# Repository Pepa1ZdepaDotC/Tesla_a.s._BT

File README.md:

# Tesla 1128A repair and BT upgrade
 **Goals:**
 - Repair radio into its original state.
 - Add a MCU capable of BT
 - Enhance the entire radio with, for example LCD, modern AMP IC

[Schematic](https://github.com/Pepa1ZdepaDotC/Tesla_BT/blob/main/Tesla_rev_2/Tesla_sextant_BT.pdf)

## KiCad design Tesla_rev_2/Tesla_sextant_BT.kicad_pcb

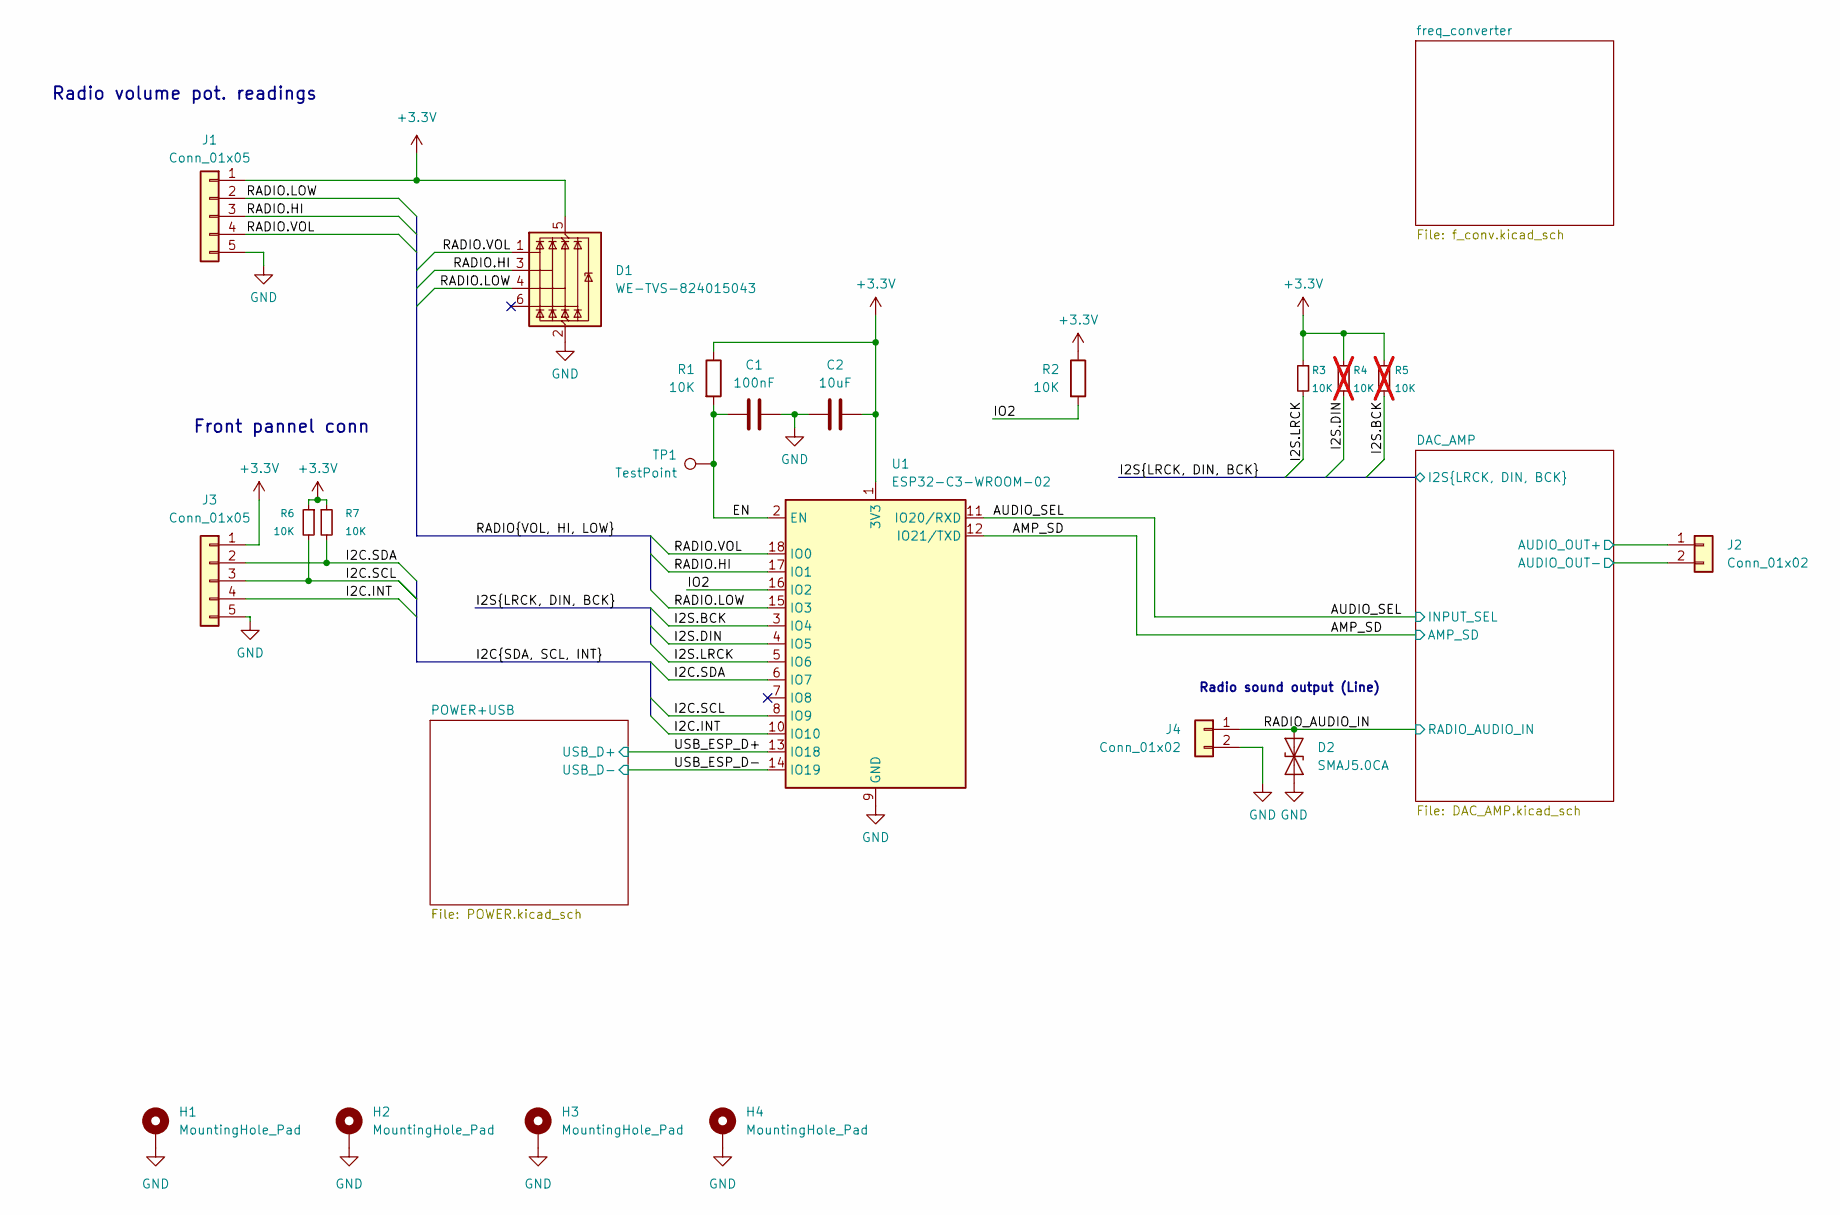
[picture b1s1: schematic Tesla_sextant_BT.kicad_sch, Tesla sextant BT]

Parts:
C1: 100nF; C_0805_2012Metric
C2: 10uF; C_0805_2012Metric
D1: WE-TVS-824015043; SOT-23-6
D2: SMAJ5.0CA; D_SMA
H1, H2, H3, H4: MountingHole_Pad; MountingHole_4.3mm_M4_DIN965_Pad_TopBottom
J1, J3: Conn_01x05; PinSocket_1x05_P2.00mm_Vertical
J2, J4: Conn_01x02; Conn_Solder_1x02_SMD
R1, R2, R3, R6, R7: 10K; C_0805_2012Metric
R4, R5: 10K; C_0805_2012Metric; not fitted
TP1: TestPoint; TestPoint_Pad_D2.5mm
U1: ESP32-C3-WROOM-02

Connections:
+3.3V: C2.1, D1.5 (VBUS), J1.1, J3.1, R1.1, R2.1, R3.1, R4.1, R5.1, R6.1, R7.1, U1.1 (3V3); also elsewhere on the board
/AMP_SD: U1.12 (IO21/TXD); also elsewhere on the board
/AUDIO_SEL: U1.11 (IO20/RXD); also elsewhere on the board
/DAC_AMP/AUDIO_OUT+: J2.1; also elsewhere on the board
/DAC_AMP/AUDIO_OUT-: J2.2; also elsewhere on the board
/EN: C1.2, R1.2, TP1.1, U1.2 (EN)
/I2C.INT: J3.4, U1.10 (IO10)
/I2C.SCL: J3.3, R6.2, U1.8 (IO9)
/I2C.SDA: J3.2, R7.2, U1.6 (IO7)
/I2S.BCK: R5.2, U1.3 (IO4); also elsewhere on the board
/I2S.DIN: R4.2, U1.4 (IO5); also elsewhere on the board
/I2S.LRCK: R3.2, U1.5 (IO6); also elsewhere on the board
/IO2: R2.2, U1.16 (IO2)
/RADIO.HI: D1.3 (I/O2), J1.3, U1.17 (IO1)
/RADIO.LOW: D1.4 (I/O3), J1.2, U1.15 (IO3)
/RADIO.VOL: D1.1 (I/O1), J1.4, U1.18 (IO0)
/RADIO_AUDIO_IN: D2.1 (A1), J4.1; also elsewhere on the board
/USB_ESP_D+: U1.13 (IO18); also elsewhere on the board
/USB_ESP_D-: U1.14 (IO19); also elsewhere on the board
GND: C1.1, C2.2, D1.2 (GND), D2.2 (A2), H1.1, H2.1, H3.1, H4.1, J1.5, J3.5, J4.2, U1.9 (GND), U1.19 (GND); also elsewhere on the board

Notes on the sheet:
Radio volume pot. readings
Radio sound output (Line)
Front pannel conn

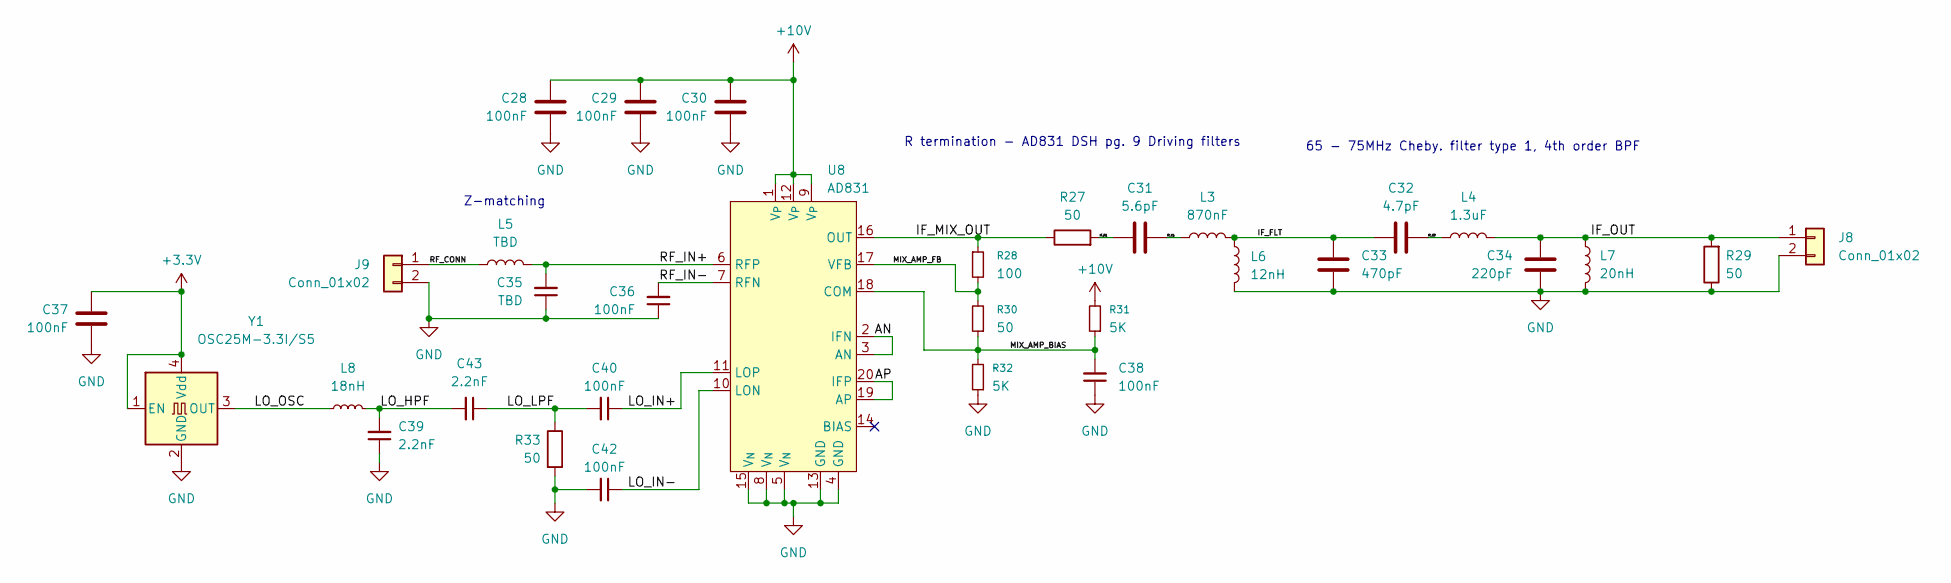
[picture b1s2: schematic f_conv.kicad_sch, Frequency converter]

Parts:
C28, C29, C30, C36, C37, C38: 100nF; C_0805_2012Metric
C31: 5.6pF; C_0603_1608Metric
C32: 4.7pF; C_0603_1608Metric
C33: 470pF; C_0603_1608Metric
C34: 220pF; C_0603_1608Metric
C35: TBD; C_0805_2012Metric
C39, C43: 2.2nF; C_0603_1608Metric
C40, C42: 100nF; C_0603_1608Metric
J8, J9: Conn_01x02; Conn_Solder_1x02_SMD
L3: 870nF; L_0805_2012Metric; Part_num DL0805-0.082
L4: 1.3uF; L_0805_2012Metric; Part_num DL0805-1.2
L5: TBD; L_0603_1608Metric
L6: 12nH; L_0603_1608Metric; Part_num LQG18HN12NJ00D
L7: 20nH; L_0603_1608Metric
L8: 18nH; L_0603_1608Metric
R27, R29, R30, R33: 50; C_0805_2012Metric
R28: 100; C_0805_2012Metric
R31, R32: 5K; C_0805_2012Metric
U8: AD831; PLCC-20
Y1: OSC25M-3.3I/S5; Oscillator_SMD_Fordahl_DFAS15-4Pin_5.0x3.2mm_HandSoldering

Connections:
+3.3V: C37.2, Y1.1 (EN), Y1.4 (Vdd); also elsewhere on the board
+10V: C28.2, C29.2, C30.2, R31.2, U8.1 (V_{P}), U8.9 (V_{P}), U8.12 (V_{P}); also elsewhere on the board
/freq_converter/AN: U8.2 (IFN), U8.3 (AN)
/freq_converter/AP: U8.19 (AP), U8.20 (IFP)
/freq_converter/IF_C1: C31.2, L3.2
/freq_converter/IF_C3: C32.1, L4.2
/freq_converter/IF_FLT: C32.2, C33.2, L3.1, L6.2
/freq_converter/IF_MIX_OUT: R27.1, R28.1, U8.16 (OUT)
/freq_converter/IF_OUT: C34.2, J8.1, L4.1, L7.1, R29.2
/freq_converter/IF_R1: C31.1, R27.2
/freq_converter/LO_HPF: C39.2, C43.2, L8.2
/freq_converter/LO_IN+: C40.1, U8.11 (LOP)
/freq_converter/LO_IN-: C42.1, U8.10 (LON)
/freq_converter/LO_LPF: C40.2, C43.1, R33.1
/freq_converter/LO_OSC: L8.1, Y1.3 (OUT)
/freq_converter/MIX_AMP_BIAS: C38.2, R30.1, R31.1, R32.2, U8.18 (COM)
/freq_converter/MIX_AMP_FB: R28.2, R30.2, U8.17 (VFB)
/freq_converter/RF_CONN: J9.1, L5.2
/freq_converter/RF_IN+: C35.2, L5.1, U8.6 (RFP)
/freq_converter/RF_IN-: C36.2, U8.7 (RFN)
GND: C28.1, C29.1, C30.1, C33.1, C34.1, C35.1, C36.1, C37.1, C38.1, C39.1, C42.2, J8.2, J9.2, L6.1, L7.2, R29.1, R32.1, R33.2, U8.4 (GND), U8.5 (V_{N}), U8.8 (V_{N}), U8.13 (GND), U8.15 (V_{N}), Y1.2 (GND); also elsewhere on the board

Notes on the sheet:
R termination - AD831 DSH pg. 9 Driving filters
65 - 75MHz Cheby. filter type 1, 4th order BPF
Z-matching

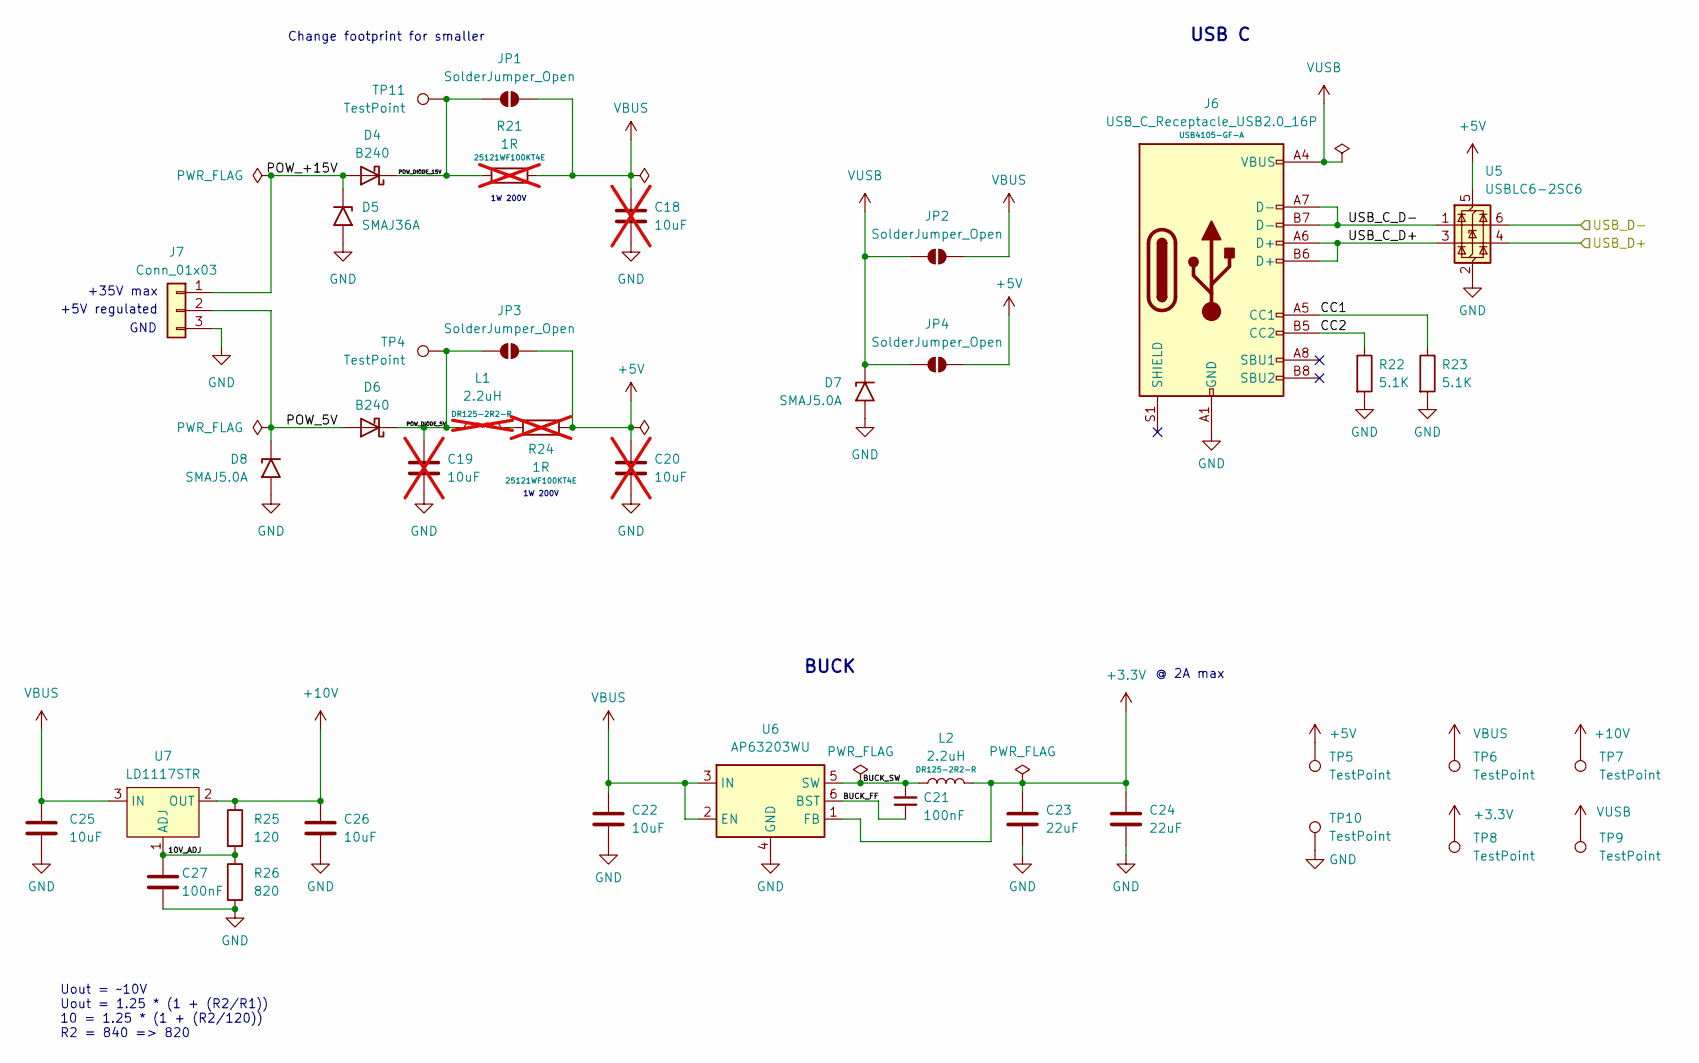
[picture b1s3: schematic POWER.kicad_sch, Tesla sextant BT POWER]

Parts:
C18, C19, C20: 10uF; C_0805_2012Metric; not fitted
C21, C27: 100nF; C_0805_2012Metric
C22, C25, C26: 10uF; C_0805_2012Metric
C23, C24: 22uF; C_0805_2012Metric
D4, D6: B240; D_SMB
D5: SMAJ36A; D_SMA
D7, D8: SMAJ5.0A; D_SMA
J6: USB_C_Receptacle_USB2.0_16P; USB_C_Receptacle_GCT_USB4105-xx-A_16P_TopMnt_Horizontal; Part_num USB4105-GF-A
J7: Conn_01x03; Conn_Solder_1x03_SMD
JP1, JP2, JP3, JP4: SolderJumper_Open; SolderJumper-2_P1.3mm_Open_TrianglePad1.0x1.5mm
L1: 2.2uH; L_12x12mm_H8mm; Part_num DR125-2R2-R; not fitted
L2: 2.2uH; L_12x12mm_H8mm; Part_num DR125-2R2-R
R21, R24: 1R; R_2512_6332Metric; Part_num 25121WF100KT4E; not fitted
R22, R23: 5.1K; C_0805_2012Metric
R25: 120; C_0805_2012Metric
R26: 820; C_0805_2012Metric
TP4, TP5, TP6, TP7, TP8, TP9, TP10, TP11: TestPoint; TestPoint_Pad_D2.5mm
U5: USBLC6-2SC6; SOT-23-6
U6: AP63203WU; TSOT-23-6
U7: LD1117STR; SOT-223

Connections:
+3.3V: C23.1, C24.1, L2.2, TP8.1, U6.1 (FB); also elsewhere on the board
+5V: C20.1, JP3.2 (B), JP4.2 (B), R24.1, TP5.1, U5.5 (VBUS); also elsewhere on the board
+10V: C26.1, R25.1, TP7.1, U7.2 (OUT), U7.4 (OUT); also elsewhere on the board
/POWER+USB/10V_ADJ: C27.1, R25.2, R26.1, U7.1 (ADJ)
/POWER+USB/BUCK_FF: C21.1, U6.6 (BST)
/POWER+USB/BUCK_SW: C21.2, L2.1, U6.5 (SW)
/POWER+USB/CC1: J6.A5 (CC1), R23.1
/POWER+USB/CC2: J6.B5 (CC2), R22.1
/POWER+USB/POW_5V: D6.2 (A), D8.1 (A1), J7.2
/POWER+USB/POW_+15V: D4.2 (A), D5.1 (A1), J7.1
/POWER+USB/POW_DIODE_5V: C19.1, D6.1 (K), JP3.1 (A), L1.1, TP4.1
/POWER+USB/POW_DIODE_15V: D4.1 (K), JP1.1 (A), R21.2, TP11.1
/POWER+USB/USB_C_D+: J6.A6 (D+), J6.B6 (D+), U5.3 (I/O2)
/POWER+USB/USB_C_D-: J6.A7 (D-), J6.B7 (D-), U5.1 (I/O1)
/USB_ESP_D+: U5.4 (I/O2); also elsewhere on the board
/USB_ESP_D-: U5.6 (I/O1); also elsewhere on the board
GND: C18.2, C19.2, C20.2, C22.2, C23.2, C24.2, C25.2, C26.2, C27.2, D5.2 (A2), D7.2 (A2), D8.2 (A2), J6.A1 (GND), J6.A12 (GND), J6.B1 (GND), J6.B12 (GND), J7.3, R22.2, R23.2, R26.2, TP10.1, U5.2 (GND), U6.4 (GND); also elsewhere on the board
unnamed: L1.2, R24.2
VBUS: C18.1, C22.1, C25.1, JP1.2 (B), JP2.2 (B), R21.1, TP6.1, U6.2 (EN), U6.3 (IN), U7.3 (IN)
VUSB: D7.1 (A1), J6.A4 (VBUS), J6.A9 (VBUS), J6.B4 (VBUS), J6.B9 (VBUS), JP2.1 (A), JP4.1 (A), TP9.1

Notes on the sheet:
Uout = ~10V Uout = 1.25 * (1 + (R2/R1)) 10 = 1.25 * (1 + (R2/120)) R2 = 840 => 820
@ 2A max
+5V regulated
GND
1W 200V
+35V max
Change footprint for smaller
BUCK
USB C

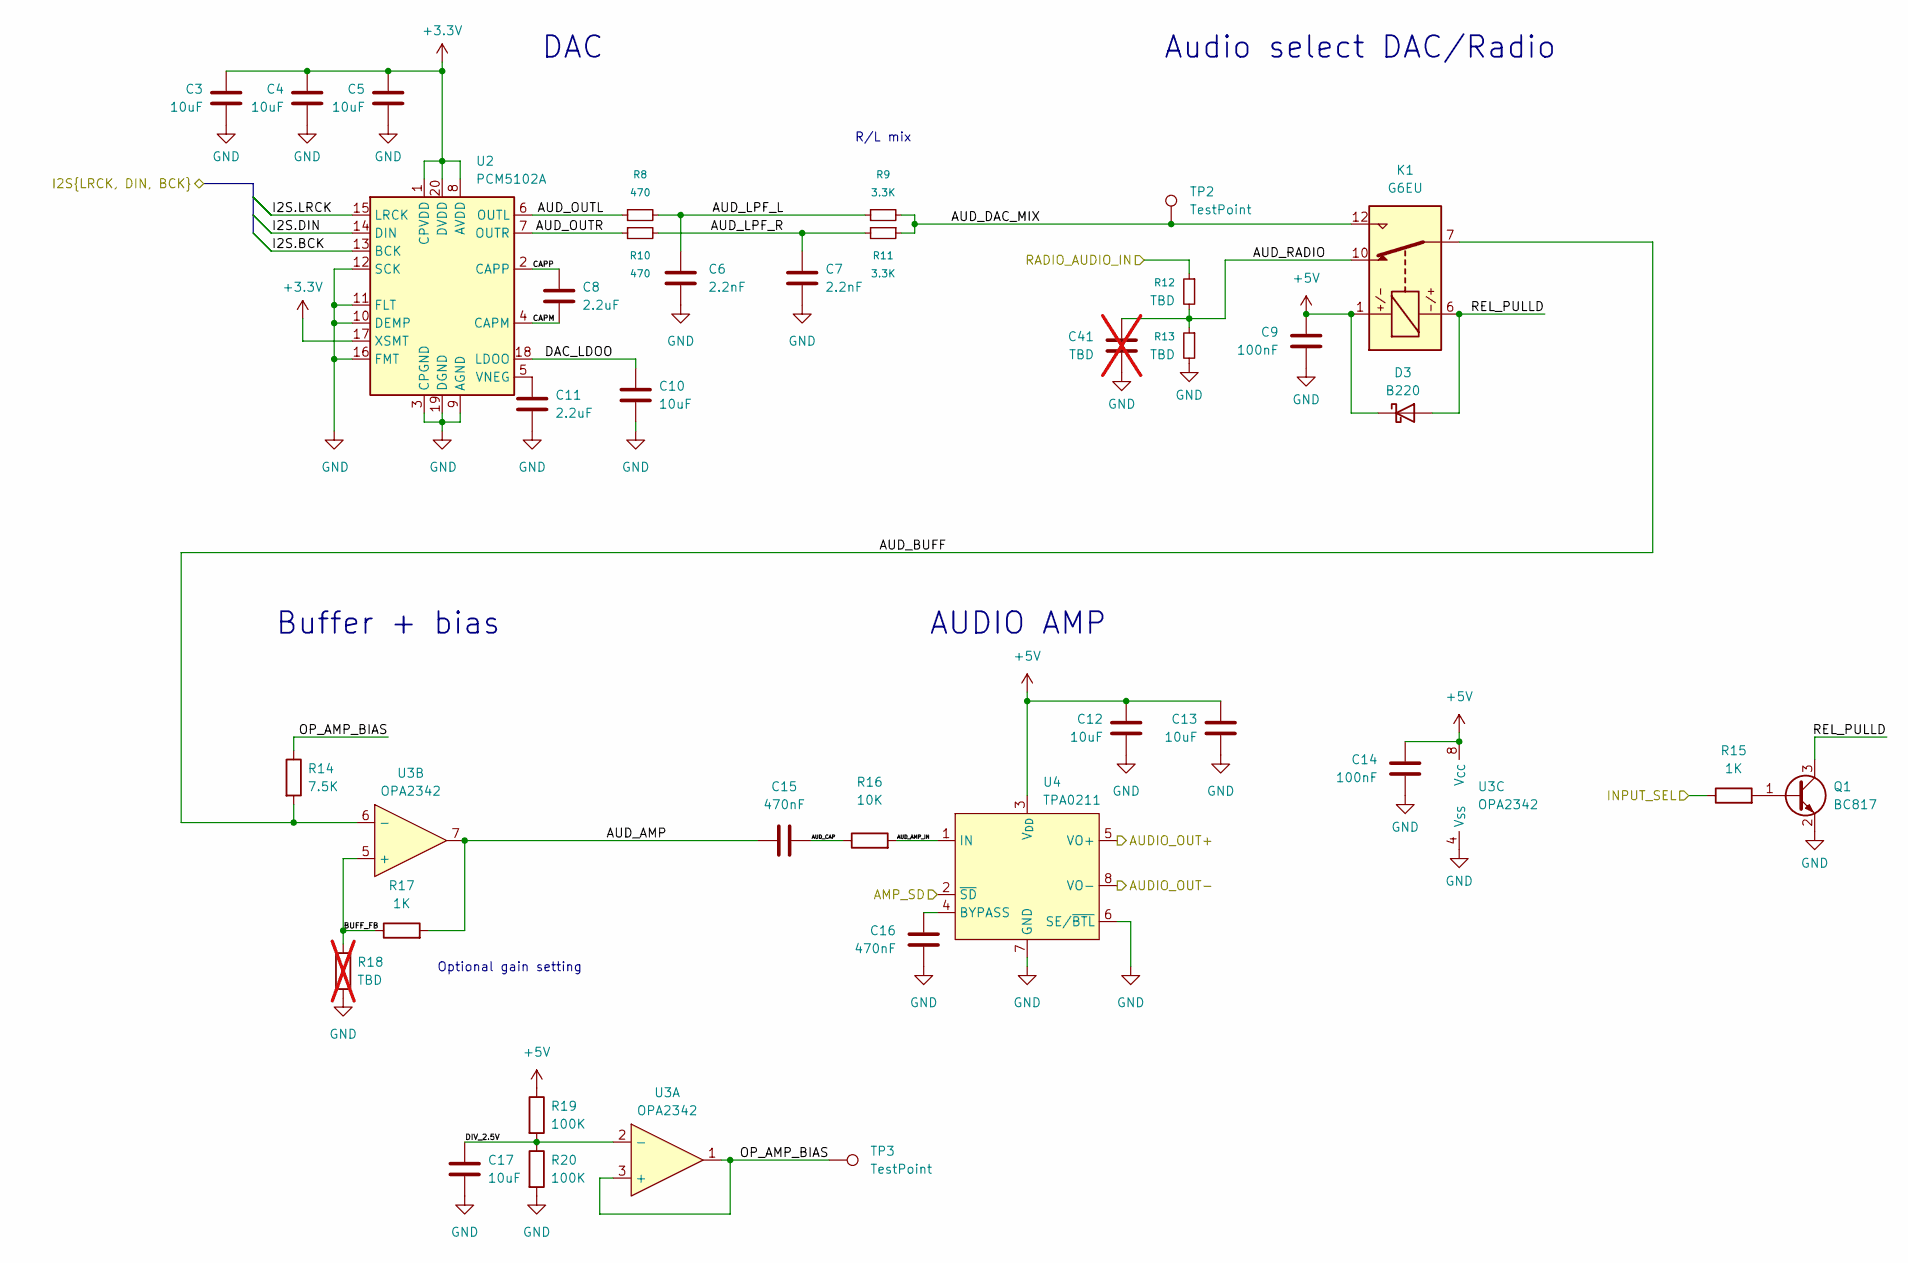
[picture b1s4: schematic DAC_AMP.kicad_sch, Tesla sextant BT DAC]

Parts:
C3, C4, C5, C10, C12, C13, C17: 10uF; C_0805_2012Metric
C6, C7: 2.2nF; C_0805_2012Metric
C8, C11: 2.2uF; C_0805_2012Metric
C9, C14: 100nF; C_0805_2012Metric
C15, C16: 470nF; C_0805_2012Metric
C41: TBD; C_0805_2012Metric; not fitted
D3: B220; D_SMB
K1: G6EU; Relay_SPDT_Omron_G6E
Q1: BC817; SOT-23
R8, R10: 470; C_0805_2012Metric
R9, R11: 3.3K; C_0805_2012Metric
R12, R13: TBD; R_0805_2012Metric
R14: 7.5K; C_0805_2012Metric
R15, R17: 1K; C_0805_2012Metric
R16: 10K; C_0805_2012Metric
R18: TBD; C_0805_2012Metric; not fitted
R19, R20: 100K; C_0805_2012Metric
TP2, TP3: TestPoint; TestPoint_Pad_D2.5mm
U2: PCM5102A; TSSOP-20_4.4x6.5mm_P0.65mm
U3: OPA2342; SOIC-8_3.9x4.9mm_P1.27mm
U4: TPA0211; HVSSOP-8-1EP_3x3mm_P0.65mm_EP1.57x1.89mm_ThermalVias

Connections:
+3.3V: C3.1, C4.1, C5.1, U2.1 (CPVDD), U2.8 (AVDD), U2.17 (XSMT), U2.20 (DVDD); also elsewhere on the board
+5V: C9.1, C12.1, C13.1, C14.1, D3.1 (K), K1.1, R19.1, U3.8 (V_{CC}), U4.3 (V_{DD}); also elsewhere on the board
/AMP_SD: U4.2 (~SD); also elsewhere on the board
/AUDIO_SEL: R15.1; also elsewhere on the board
/DAC_AMP/AUDIO_OUT+: U4.5 (VO+); also elsewhere on the board
/DAC_AMP/AUDIO_OUT-: U4.8 (VO-); also elsewhere on the board
/DAC_AMP/AUD_AMP: C15.1, R17.2, U3.7
/DAC_AMP/AUD_AMP_IN: R16.2, U4.1 (IN)
/DAC_AMP/AUD_BUFF: K1.7, R14.2, U3.6 (-)
/DAC_AMP/AUD_CAP: C15.2, R16.1
/DAC_AMP/AUD_DAC_MIX: K1.12, R9.2, R11.1, TP2.1
/DAC_AMP/AUD_LPF_L: C6.1, R8.2, R9.1
/DAC_AMP/AUD_LPF_R: C7.1, R10.2, R11.2
/DAC_AMP/AUD_OUTL: R8.1, U2.6 (OUTL)
/DAC_AMP/AUD_OUTR: R10.1, U2.7 (OUTR)
/DAC_AMP/AUD_RADIO: C41.1, K1.10, R12.2, R13.1
/DAC_AMP/BUFF_FB: R17.1, R18.2, U3.5 (+)
/DAC_AMP/CAPM: C8.2, U2.4 (CAPM)
/DAC_AMP/CAPP: C8.1, U2.2 (CAPP)
/DAC_AMP/DAC_LDOO: C10.1, U2.18 (LDOO)
/DAC_AMP/DIV_2.5V: C17.1, R19.2, R20.1, U3.2 (-)
/DAC_AMP/OP_AMP_BIAS: R14.1, TP3.1, U3.1, U3.3 (+)
/DAC_AMP/REL_PULLD: D3.2 (A), K1.6, Q1.3 (C)
/I2S.BCK: U2.13 (BCK); also elsewhere on the board
/I2S.DIN: U2.14 (DIN); also elsewhere on the board
/I2S.LRCK: U2.15 (LRCK); also elsewhere on the board
/RADIO_AUDIO_IN: R12.1; also elsewhere on the board
GND: C3.2, C4.2, C5.2, C6.2, C7.2, C9.2, C10.2, C11.2, C12.2, C13.2, C14.2, C16.2, C17.2, C41.2, Q1.2 (E), R13.2, R18.1, R20.2, U2.3 (CPGND), U2.9 (AGND), U2.10 (DEMP), U2.11 (FLT), U2.12 (SCK), U2.16 (FMT), U2.19 (DGND), U3.4 (V_{SS}), U4.6 (SE/~BTL), U4.7 (GND); also elsewhere on the board
unnamed: Q1.1 (B), R15.2
unnamed: C11.1, U2.5 (VNEG)
unnamed: C16.1, U4.4 (BYPASS)

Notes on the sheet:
Audio select DAC/Radio
AUDIO AMP
R/L mix
Buffer + bias
DAC
Optional gain setting

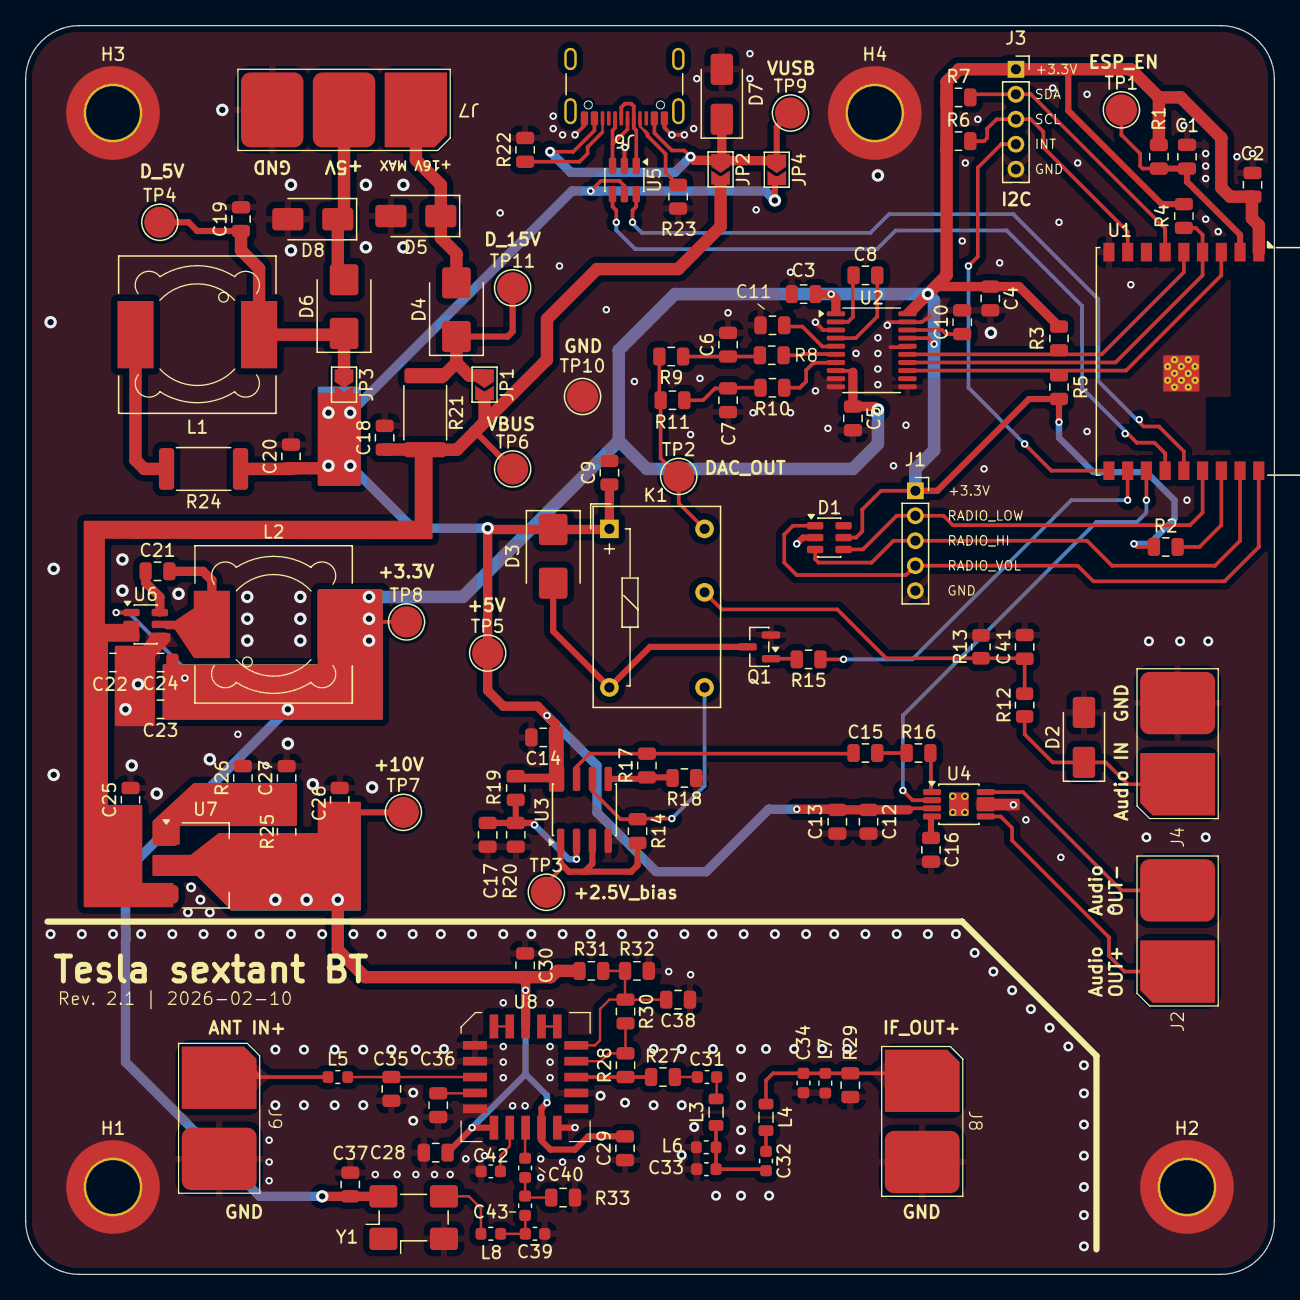
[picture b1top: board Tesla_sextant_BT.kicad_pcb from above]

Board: 4 copper layers, 100.0 x 100.0 mm, 130 parts (0 on the bottom side), 74 nets.

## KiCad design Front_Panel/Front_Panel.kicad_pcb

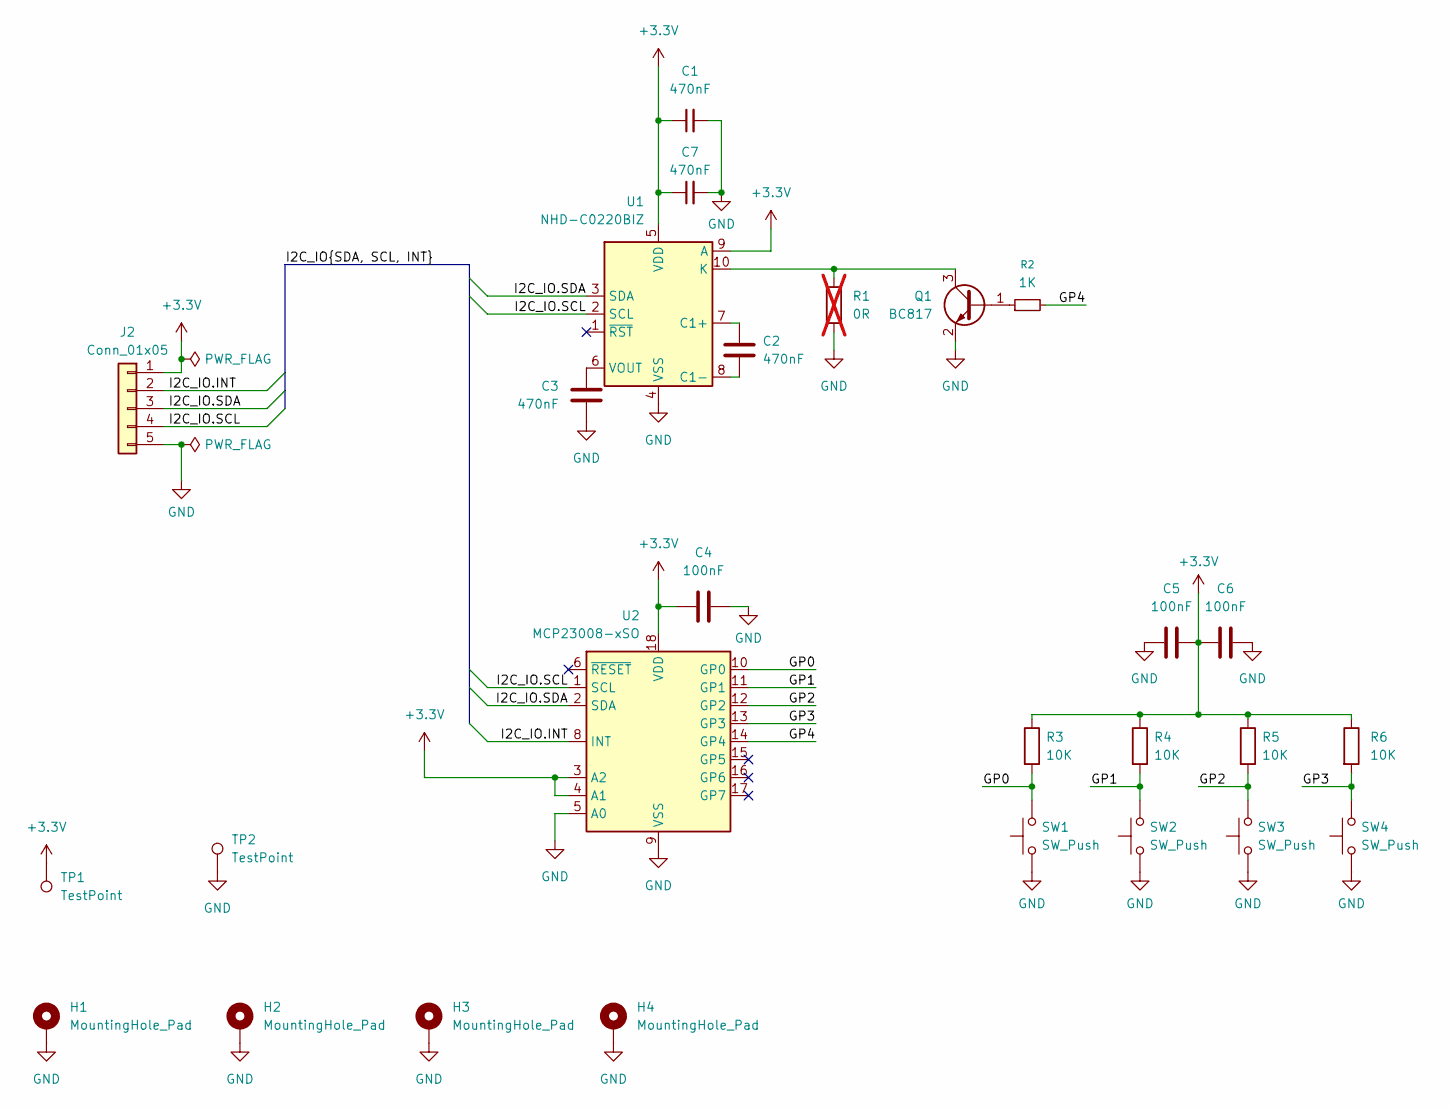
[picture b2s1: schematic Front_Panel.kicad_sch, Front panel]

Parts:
C1, C2, C3, C7: 470nF; C_0805_2012Metric
C4, C5, C6: 100nF; C_0805_2012Metric
H1, H2, H3, H4: MountingHole_Pad; MountingHole_4.3mm_M4_DIN965_Pad_TopBottom
J2: Conn_01x05; PinSocket_1x05_P2.54mm_Vertical
Q1: BC817; SOT-23
R1: 0R; R_0805_2012Metric; not fitted
R2: 1K; R_0805_2012Metric
R3, R4, R5, R6: 10K; R_0805_2012Metric
SW1, SW2, SW3, SW4: SW_Push; SW_PUSH-12mm_Wuerth-430476085716
TP1, TP2: TestPoint; TestPoint_Pad_D3.0mm
U1: NHD-C0220BIZ; NHD-C0220BiZ
U2: MCP23008-xSO; SOIC-18W_7.5x11.6mm_P1.27mm

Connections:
+3.3V: C1.1, C4.1, C5.2, C6.1, C7.1, J2.1, R3.1, R4.1, R5.1, R6.1, TP1.1, U1.5 (VDD), U1.9 (A), U2.3 (A2), U2.4 (A1), U2.18 (VDD)
/GP0: R3.2, SW1.2, U2.10 (GP0)
/GP1: R4.2, SW2.2, U2.11 (GP1)
/GP2: R5.2, SW3.2, U2.12 (GP2)
/GP3: R6.2, SW4.2, U2.13 (GP3)
/GP4: R2.2, U2.14 (GP4)
/I2C_IO.INT: J2.2, U2.8 (INT)
/I2C_IO.SCL: J2.4, U1.2 (SCL), U2.1 (SCL)
/I2C_IO.SDA: J2.3, U1.3 (SDA), U2.2 (SDA)
GND: C1.2, C3.2, C4.2, C5.1, C6.2, C7.2, H1.1, H2.1, H3.1, H4.1, J2.5, Q1.2 (E), R1.2, SW1.1, SW2.1, SW3.1, SW4.1, TP2.1, U1.4 (VSS), U2.5 (A0), U2.9 (VSS)
unnamed: Q1.1 (B), R2.1
unnamed: Q1.3 (C), R1.1, U1.10 (K)
unnamed: C2.1, U1.7 (C1+)
unnamed: C2.2, U1.8 (C1-)
unnamed: C3.1, U1.6 (VOUT)

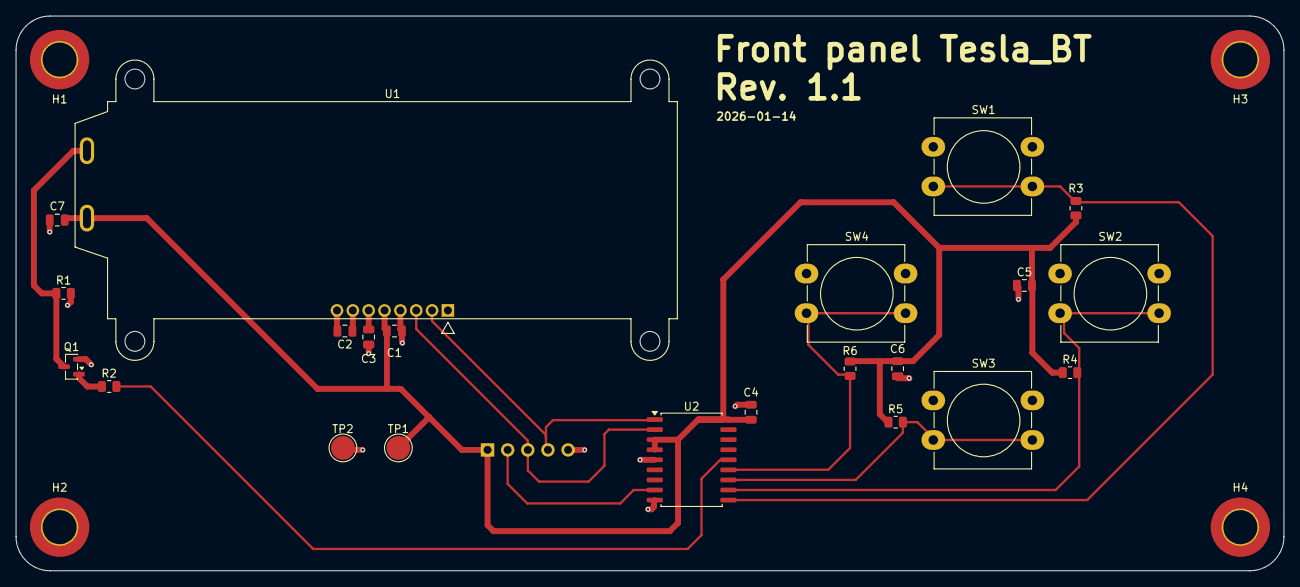
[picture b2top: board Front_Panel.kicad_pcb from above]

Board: 2 copper layers, 160.0 x 70.0 mm, 27 parts (1 on the bottom side), 15 nets.

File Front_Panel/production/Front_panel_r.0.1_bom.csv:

Designator,Footprint,Quantity,Value,LCSC Part #
"C1, C2, C3, C7",0805,4,470nF,
"C4, C5, C6",0805,3,100nF,
J2,PinSocket_1x05_P2.54mm_Vertical,1,Conn_01x05,
Q1,SOT-23,1,BC817,
R1,0805,1,0R,
R2,0805,1,1K,
"R3, R4, R5, R6",0805,4,10K,
"SW1, SW2, SW3, SW4",SW_PUSH-12mm_Wuerth-430476085716,4,SW_Push,
"TP1, TP2",TestPoint_Pad_D3.0mm,2,TestPoint,
U1,NHD-C0220BiZ,1,NHD-C0220BIZ,
U2,SOIC-18W_7.5x11.6mm_P1.27mm,1,MCP23008-xSO,

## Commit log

2025-11-29 Changed link to schematic pdf
2025-11-29 Refactor
2025-12-07 Added photos of radio
2025-12-07 Updated photos
2025-12-17 revision 3
2025-12-19 revision 3.1
2026-02-05 Rev 2.3, schematic and footprint fixes, prepared for layout
2026-02-10 added PCB layou
2026-02-11 schematic fixes and pcb layout
2026-02-11 Add images to README
2026-02-11 Remove goals section from README
